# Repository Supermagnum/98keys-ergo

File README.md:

# 94keys-ergo

Moved to:

https://github.com/Supermagnum/Europe-ergo

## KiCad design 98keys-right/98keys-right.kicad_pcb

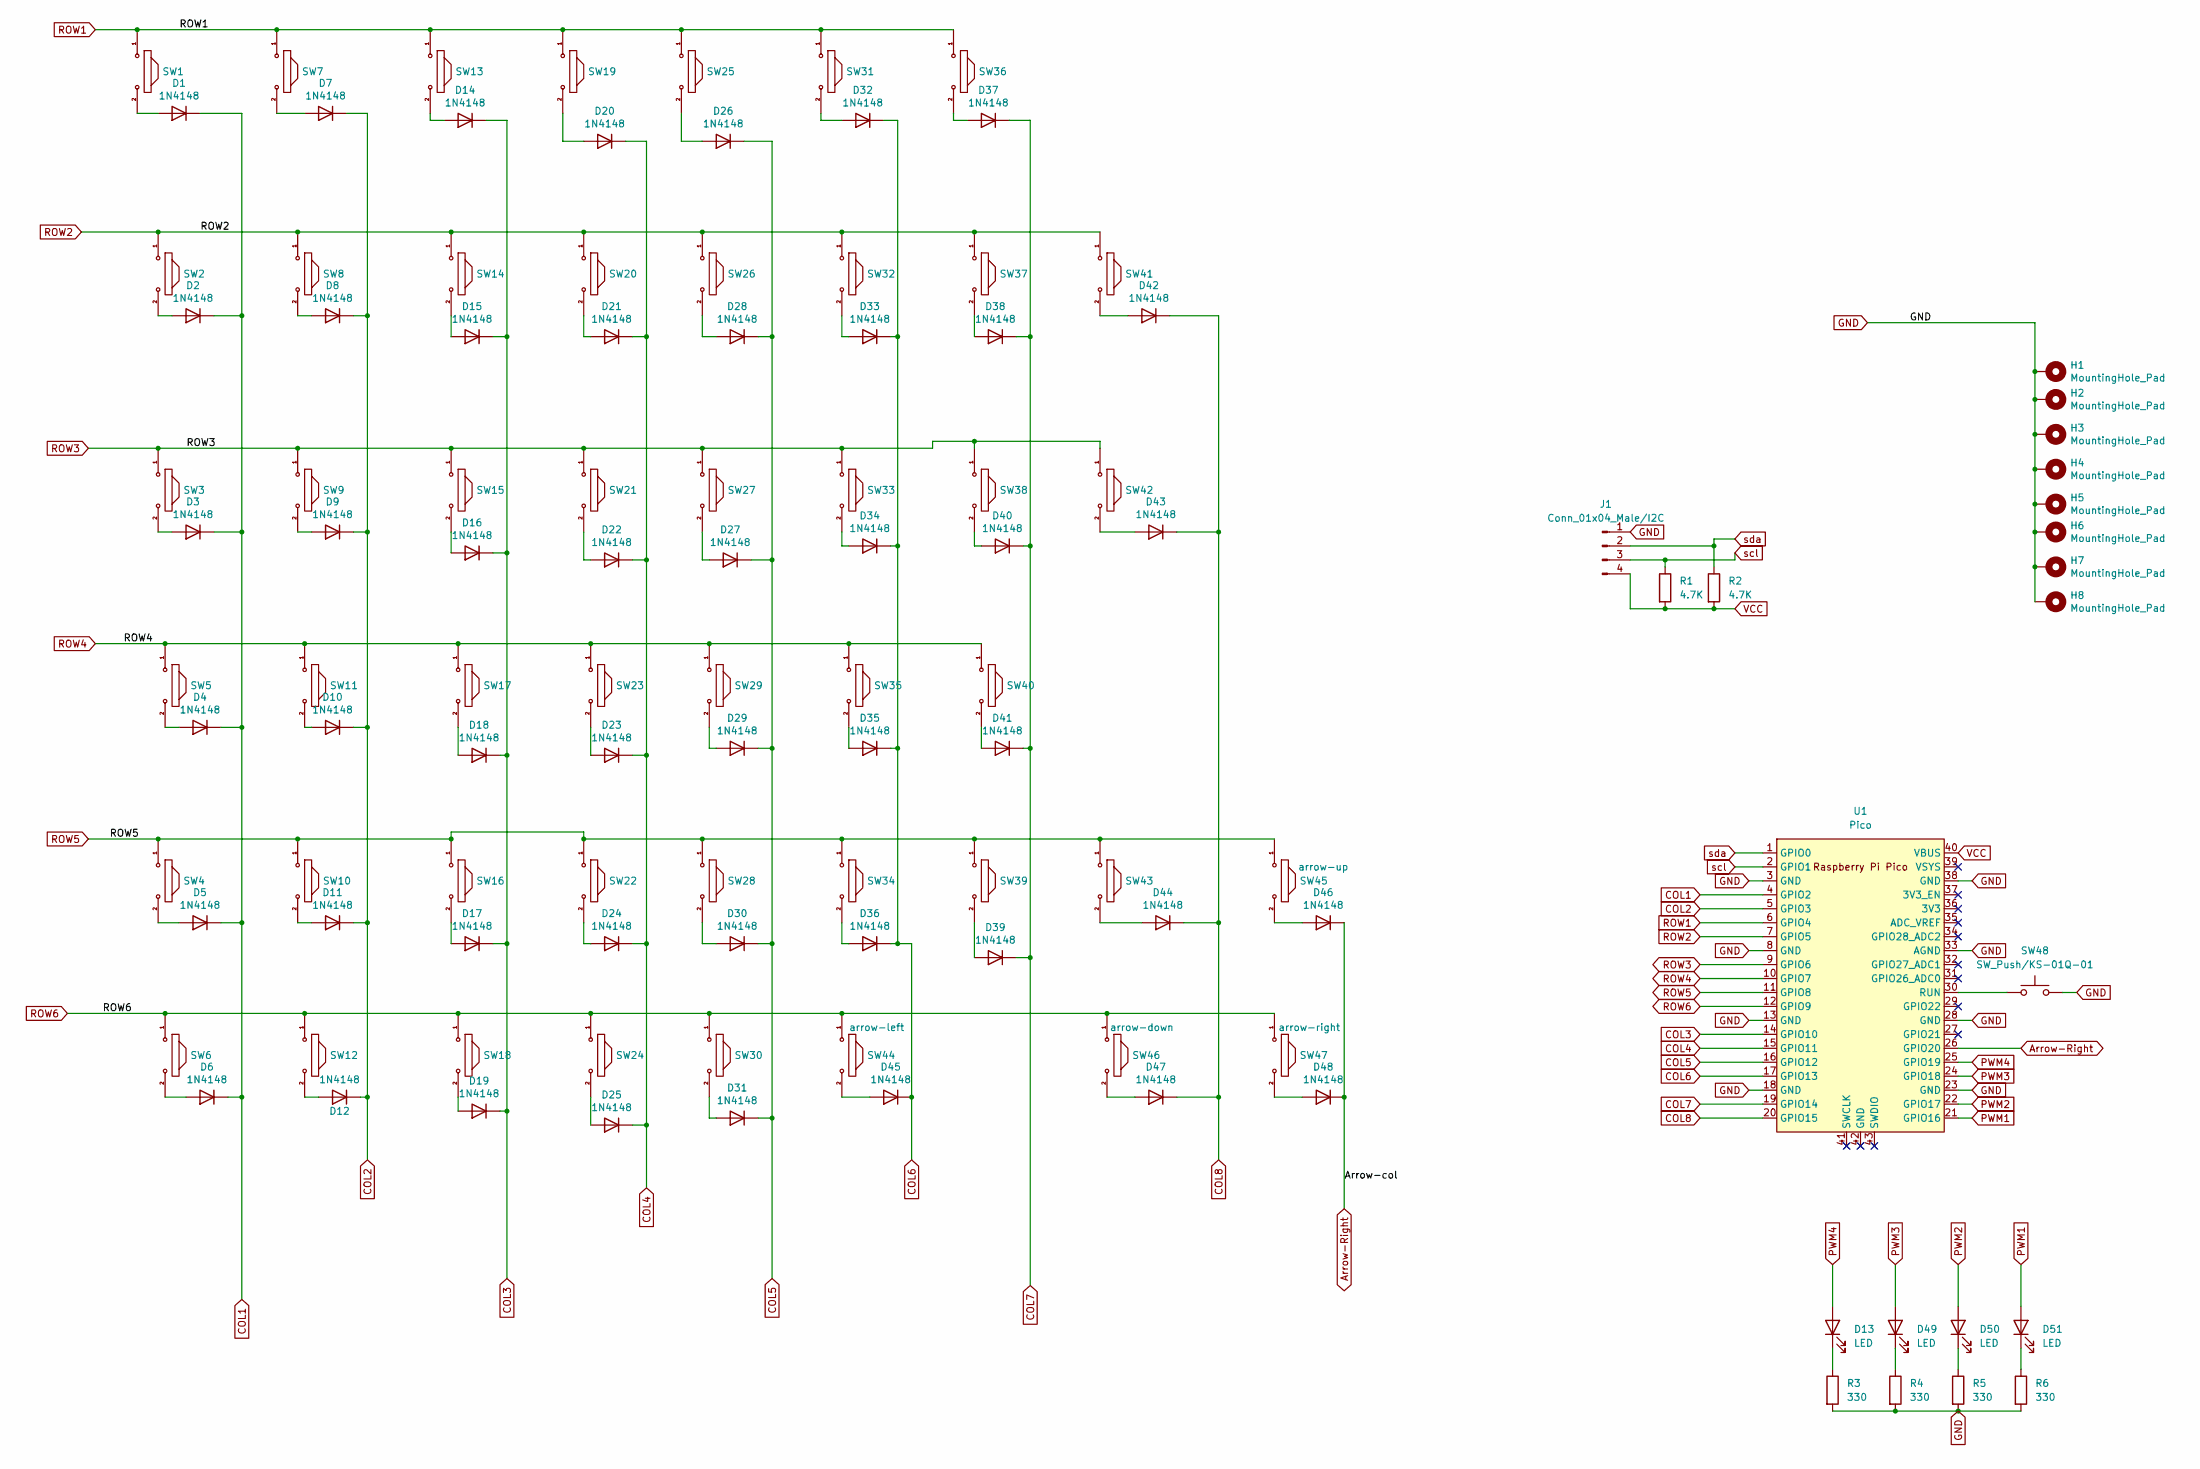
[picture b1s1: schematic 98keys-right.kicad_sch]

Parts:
D1, D2, D3, D4, D5, D6, D7, D8, D9, D10, D11, D12, D14, D15, D16, D17, D18, D19, D20, D21, D22, D23, D24, D25, D26, D27, D28, D29, D30, D31, D32, D33, D34, D35, D36, D37, D38, D39, D40, D41, D42, D43, D44, D45, D46, D47, D48: 1N4148; D_DO-35_SOD27_P7.62mm_Horizontal
D13, D49, D50, D51: LED; D_DO-34_SOD68_P2.54mm_Vertical_KathodeUp
H1, H2, H3, H4, H5, H6, H7, H8: MountingHole_Pad; MountingHole_4.3mm_M4_DIN965_Pad
J1: Conn_01x04_Male/I2C; Jack_3.5mm_CUI_SJ1-43514_Horizontal
R1, R2: 4.7K; R_Axial_DIN0204_L3.6mm_D1.6mm_P5.08mm_Horizontal
R3, R4, R5, R6: 330; R_Axial_DIN0204_L3.6mm_D1.6mm_P5.08mm_Horizontal
SW1, SW6, SW7, SW8, SW9, SW10, SW11, SW12, SW13, SW14, SW15, SW16, SW17, SW18, SW19, SW20, SW21, SW22, SW23, SW24, SW25, SW26, SW27, SW28, SW29, SW30, SW31, SW32, SW33, SW34, SW35, SW36, SW37, SW38, SW39, SW40, SW41, SW44, SW45, SW46, SW47: MX-NO-LED; SW_Cherry_MX_1.00u_PCB
SW2, SW3, SW4, SW5, SW42, SW43: MX-NO-LED; SW_Cherry_MX_1.50u_PCB
SW48: SW_Push/KS-01Q-01; Push_E-Switch_KS01Q01
U1: Pico; RPi_Pico_SMD_TH

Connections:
Arrow-Right: D46.1 (K), D48.1 (K), U1.26 (GPIO20)
COL1: D1.1 (K), D2.1 (K), D3.1 (K), D4.1 (K), D5.1 (K), D6.1 (K), U1.4 (GPIO2)
COL2: D7.1 (K), D8.1 (K), D9.1 (K), D10.1 (K), D11.1 (K), D12.1 (K), U1.5 (GPIO3)
COL3: D14.1 (K), D15.1 (K), D16.1 (K), D17.1 (K), D18.1 (K), D19.1 (K), U1.14 (GPIO10)
COL4: D20.1 (K), D21.1 (K), D22.1 (K), D23.1 (K), D24.1 (K), D25.1 (K), U1.15 (GPIO11)
COL5: D26.1 (K), D27.1 (K), D28.1 (K), D29.1 (K), D30.1 (K), D31.1 (K), U1.16 (GPIO12)
COL6: D32.1 (K), D33.1 (K), D34.1 (K), D35.1 (K), D36.1 (K), D45.1 (K), U1.17 (GPIO13)
COL7: D37.1 (K), D38.1 (K), D39.1 (K), D40.1 (K), D41.1 (K), U1.19 (GPIO14)
COL8: D42.1 (K), D43.1 (K), D44.1 (K), D47.1 (K), U1.20 (GPIO15)
GND: H1.1, H2.1, H3.1, H4.1, H5.1, H6.1, H7.1, H8.1, J1.1, R3.2, R4.2, R5.2, R6.2, SW48.2, U1.3 (GND), U1.8 (GND), U1.13 (GND), U1.18 (GND), U1.23 (GND), U1.28 (GND), U1.33 (AGND), U1.38 (GND)
unnamed: D1.2 (A), SW1.2
unnamed: D2.2 (A), SW2.2
unnamed: D3.2 (A), SW3.2
unnamed: D4.2 (A), SW5.2
unnamed: D5.2 (A), SW4.2
unnamed: D6.2 (A), SW6.2
unnamed: D7.2 (A), SW7.2
unnamed: D8.2 (A), SW8.2
unnamed: D9.2 (A), SW9.2
unnamed: D10.2 (A), SW11.2
unnamed: D11.2 (A), SW10.2
unnamed: D12.2 (A), SW12.2
unnamed: D13.1 (K), R3.1
unnamed: D14.2 (A), SW13.2
unnamed: D15.2 (A), SW14.2
unnamed: D16.2 (A), SW15.2
unnamed: D17.2 (A), SW16.2
unnamed: D18.2 (A), SW17.2
unnamed: D19.2 (A), SW18.2
unnamed: D20.2 (A), SW19.2
unnamed: D21.2 (A), SW20.2
unnamed: D22.2 (A), SW21.2
unnamed: D23.2 (A), SW23.2
unnamed: D24.2 (A), SW22.2
unnamed: D25.2 (A), SW24.2
unnamed: D26.2 (A), SW25.2
unnamed: D27.2 (A), SW27.2
unnamed: D28.2 (A), SW26.2
unnamed: D29.2 (A), SW29.2
unnamed: D30.2 (A), SW28.2
unnamed: D31.2 (A), SW30.2
unnamed: D32.2 (A), SW31.2
unnamed: D33.2 (A), SW32.2
unnamed: D34.2 (A), SW33.2
unnamed: D35.2 (A), SW35.2
unnamed: D36.2 (A), SW34.2
unnamed: D37.2 (A), SW36.2
unnamed: D38.2 (A), SW37.2
unnamed: D39.2 (A), SW39.2
unnamed: D40.2 (A), SW38.2
unnamed: D41.2 (A), SW40.2
unnamed: D42.2 (A), SW41.2
unnamed: D43.2 (A), SW42.2
unnamed: D44.2 (A), SW43.2
unnamed: D45.2 (A), SW44.2
unnamed: D46.2 (A), SW45.2
unnamed: D47.2 (A), SW46.2
unnamed: D48.2 (A), SW47.2
unnamed: D49.1 (K), R4.1
unnamed: D50.1 (K), R5.1
unnamed: D51.1 (K), R6.1
unnamed: SW48.1, U1.30 (RUN)
PWM1: D51.2 (A), U1.21 (GPIO16)
PWM2: D50.2 (A), U1.22 (GPIO17)
PWM3: D49.2 (A), U1.24 (GPIO18)
PWM4: D13.2 (A), U1.25 (GPIO19)
ROW1: SW1.1, SW7.1, SW13.1, SW19.1, SW25.1, SW31.1, SW36.1, U1.6 (GPIO4)
ROW2: SW2.1, SW8.1, SW14.1, SW20.1, SW26.1, SW32.1, SW37.1, SW41.1, U1.7 (GPIO5)
ROW3: SW3.1, SW9.1, SW15.1, SW21.1, SW27.1, SW33.1, SW38.1, SW42.1, U1.9 (GPIO6)
ROW4: SW5.1, SW11.1, SW17.1, SW23.1, SW29.1, SW35.1, SW40.1, U1.10 (GPIO7)
ROW5: SW4.1, SW10.1, SW16.1, SW22.1, SW28.1, SW34.1, SW39.1, SW43.1, SW45.1, U1.11 (GPIO8)
ROW6: SW6.1, SW12.1, SW18.1, SW24.1, SW30.1, SW44.1, SW46.1, SW47.1, U1.12 (GPIO9)
VCC: J1.4, R1.2, R2.2, U1.40 (VBUS)
scl: J1.3, R1.1, U1.2 (GPIO1)
sda: J1.2, R2.1, U1.1 (GPIO0)

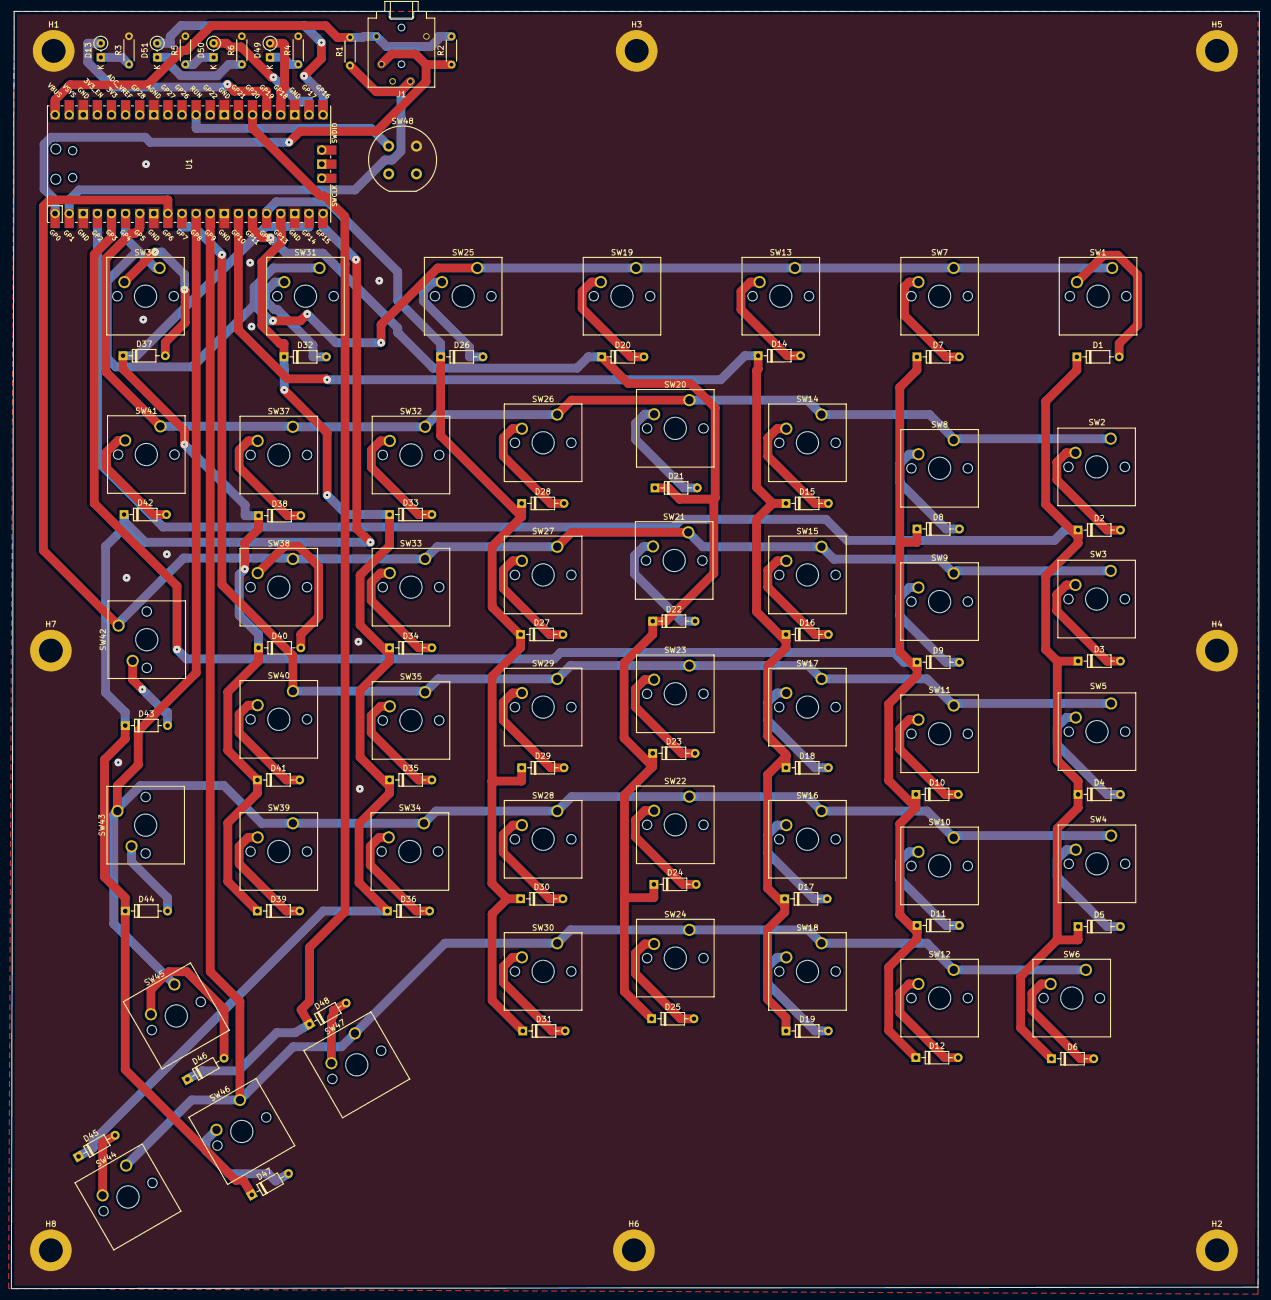
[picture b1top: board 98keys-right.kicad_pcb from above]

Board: 2 copper layers, 224.8 x 230.0 mm, 115 parts (0 on the bottom side), 75 nets.

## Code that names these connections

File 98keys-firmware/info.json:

{
    "manufacturer": "Supermagnum",
    "keyboard_name": "98keys",
    "maintainer": "Supermagnum",
    "bootloader": "rp2040",
    "diode_direction": "ROW2COL",
    "features": {
        "bootmagic": true,
        "command": false,
        "console": false,
        "extrakey": true,
        "mousekey": true,
        "nkro": true
    },
    "matrix_pins": {
        "cols": ["GPIO2", "GPIO3", "GPIO10", "GPIO11" , "GPIO12" , "GPIO13" , "GPIO14 , "GPIO15" ,"GPIO20" ]
        "rows": ["GPIO4", "GPIO5", "GPIO6", "GPIO7" , "GPIO8" , "GPIO9"]
    },
    "processor": "RP2040",
    "url": "https://github.com/Supermagnum/98keys-ergo",
    "usb": {
        "device_version": "1.0.0",
        "pid": "0x0000",
        "vid": "0xFEED"
    },
    "layouts": {
        "LAYOUT_ortho_6x9": {
            "layout": [
                { "matrix": [0, 0], "x": 0, "y": 0 },
                { "matrix": [0, 1], "x": 1, "y": 0 },
                { "matrix": [0, 2], "x": 2, "y": 0 },
                { "matrix": [0, 3], "x": 3, "y": 0 },
                { "matrix": [1, 0], "x": 0, "y": 1 },
                { "matrix": [1, 1], "x": 1, "y": 1 },
                { "matrix": [1, 2], "x": 2, "y": 1 },
                { "matrix": [1, 3], "x": 3, "y": 1 },
                { "matrix": [2, 0], "x": 0, "y": 2 },
                { "matrix": [2, 1], "x": 1, "y": 2 },
                { "matrix": [2, 2], "x": 2, "y": 2 },
                { "matrix": [2, 3], "x": 3, "y": 2 },
                { "matrix": [3, 0], "x": 0, "y": 3 },
                { "matrix": [3, 1], "x": 1, "y": 3 },
                { "matrix": [3, 2], "x": 2, "y": 3 },
                { "matrix": [3, 3], "x": 3, "y": 3 }
            ]
        }
    }
}

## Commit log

2020-09-08 Update LICENSE
2020-09-08 added files for left part.
2020-09-08 added files for right part.
2020-09-08 one side of the mirrored layout.
2020-09-09 updated files
2020-09-09 updated files, right side.
2020-09-09 added diagrams
2020-09-09 Shows how to build the connecting cable
2020-09-11 Update README.md
    Added fault message.
2020-09-12 Add files via upload
    updated files
2020-09-12 Add files via upload
    update
2020-09-12 Add files via upload
    added connecting cable
2020-09-12 Update README.md
    added links to pcb's.
2020-09-12 Delete pcb-flat-left-elec-diagram.pdf
    Removed outdated.
2020-09-12 Delete pcb-flat-right-elec-diagram.pdf
    Removed outdated
2022-11-05 Added premiliary firmware
2022-11-08 Add files via upload
    Added a attempt at creating a layout with letters/numbers.
2022-11-14 Update info.json
    Fix missing "
2022-11-14 Added pictures of both PCB's
2022-11-15 Add files via upload
    Json file for the complete keyboard, without any legends.
2022-11-27 splittable pcb.
    Added a pcb with the two halves on the same board,- easy to separate.
2022-11-29 added picture
2022-11-30 json file for vial.
2022-11-30 Added legends for LED's.
2022-11-30 added Todo
2022-12-01 move files into named keyboard folder
2022-12-01 move LAYOUT to 98keys.h, fix obvious issues
2022-12-01 add MCU and build options
2022-12-01 keymap formatting
2022-12-01 refactor LAYOUT. fixes #1
2022-12-01 add keymap include
2022-12-01 compiled "i2c_slave.h not found"
2022-12-02 Key caps sizes
    Added list of key cap sizes.
2022-12-03 Updated pcb files.
2022-12-03 change to serial comms. FULL SUCCESSFUL COMPILE
2022-12-03 Update rules.mk
    Enabled serial comm.
2022-12-03 Update config.h
    Added LED controll.
2022-12-03 Update README.md
    Firmware should work now.
2022-12-03 Update readme.md
    Update
2022-12-03 Update config.h
    corrected
2022-12-03 Update keymap.c
    remove unneeded function.
2022-12-03 Add files via upload
    added files for vial.
2022-12-03 Add files via upload
    Moved connectors, mounting holes, and raspberry's.
2022-12-03 Add files via upload
    Mechanical box and plates in progress.
2022-12-03 Add files via upload
    Keycap details.
2022-12-03 Add files via upload
    final update?
2022-12-03 Update info.json
    Added missing matrix row.
2022-12-04 Add files via upload
    Added mechanical drawings, boxes and lids, and stl files.
2022-12-04 Delete kbplate.svg
    not needed.
2022-12-04 Update README.md
    cleaned up readme.
2022-12-05 Update info.json
    small correction.
2022-12-05 Update rules.mk
    mcu and bootloaderin rules.mk is redundant,already have it in info.json
